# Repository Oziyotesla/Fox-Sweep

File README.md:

# Fox Sweep Half Swept

This is a Ferris Sweep half-swept variant with WeAct BlackPill V2.0 and QMK configuration files.

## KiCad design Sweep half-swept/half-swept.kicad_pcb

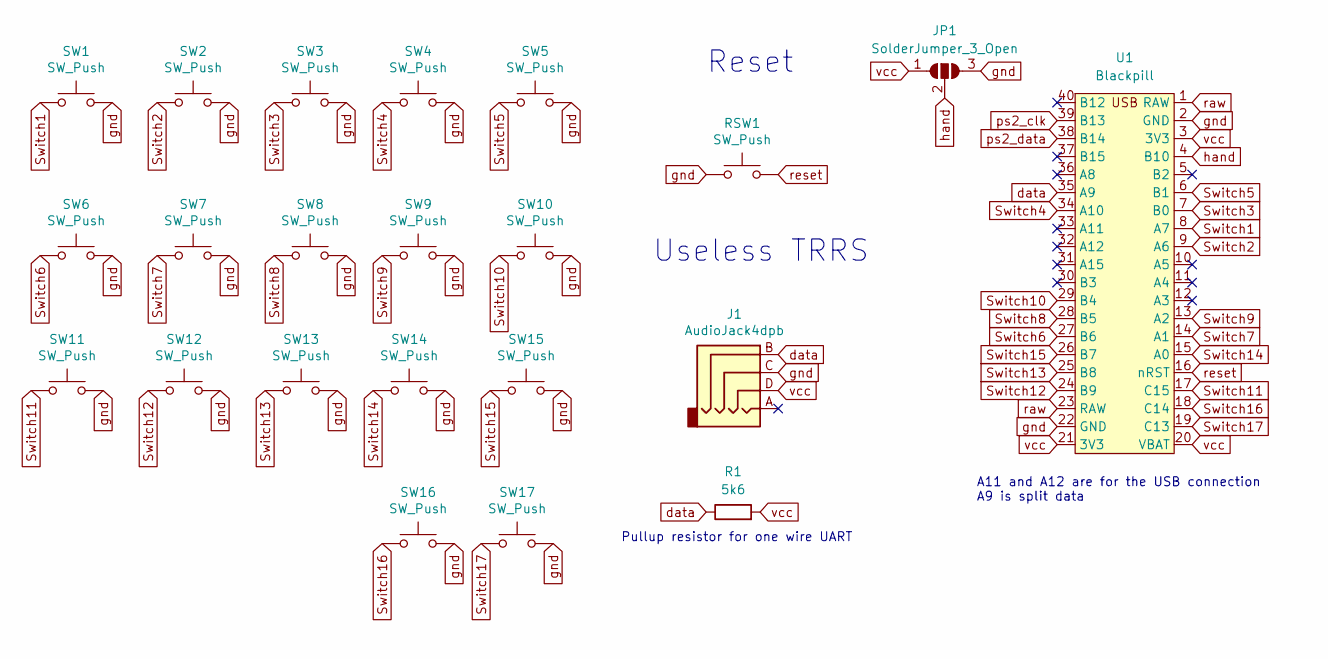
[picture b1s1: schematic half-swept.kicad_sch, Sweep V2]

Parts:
J1: AudioJack4dpb; TRRS 2side
JP1: SolderJumper_3_Open; SolderJumper-3_P1.3mm_Open_RoundedPad1.0x1.5mm
R1: 5k6; 0603 resistor
RSW1: SW_Push; ResetSW
SW1, SW2, SW3, SW4, SW5, SW6, SW7, SW8, SW9, SW10, SW11, SW12, SW13, SW14, SW15, SW16, SW17: SW_Push; SW_PG1350_rev_DPB
U1: Blackpill; Blakpill

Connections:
Switch1: SW1.1, U1.8 (A7)
Switch2: SW2.1, U1.9 (A6)
Switch3: SW3.1, U1.7 (B0)
Switch4: SW4.1, U1.34 (A10)
Switch5: SW5.1, U1.6 (B1)
Switch6: SW6.1, U1.27 (B6)
Switch7: SW7.1, U1.14 (A1)
Switch8: SW8.1, U1.28 (B5)
Switch9: SW9.1, U1.13 (A2)
Switch10: SW10.1, U1.29 (B4)
Switch11: SW11.1, U1.17 (C15)
Switch12: SW12.1, U1.24 (B9)
Switch13: SW13.1, U1.25 (B8)
Switch14: SW14.1, U1.15 (A0)
Switch15: SW15.1, U1.26 (B7)
Switch16: SW16.1, U1.18 (C14)
Switch17: SW17.1, U1.19 (C13)
data: J1.B, R1.1, U1.35 (A9)
hand: JP1.2 (C), U1.4 (B10)
ps2_clk: U1.39 (B13)
ps2_data: U1.38 (B14)
raw: U1.1 (RAW), U1.23 (RAW)
vcc: J1.D, JP1.1 (A), R1.2, U1.3 (3V3), U1.20 (VBAT), U1.21 (3V3)

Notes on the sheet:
A11 and A12 are for the USB connection A9 is split data
Reset
Useless TRRS
Pullup resistor for one wire UART

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
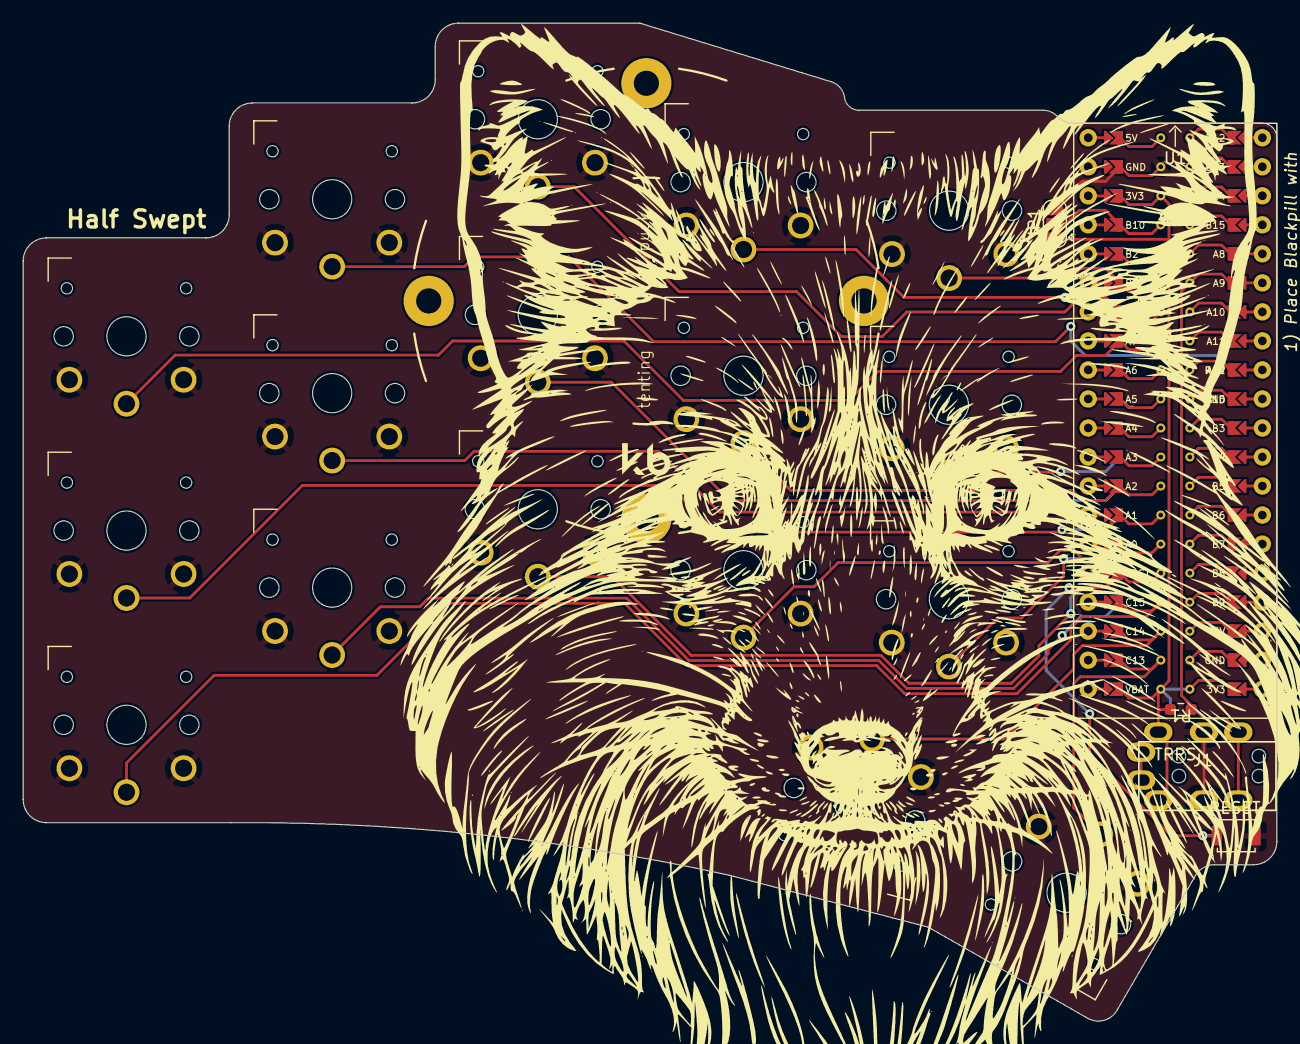
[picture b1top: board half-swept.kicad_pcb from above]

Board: 2 copper layers, 109.7 x 87.3 mm, 22 parts (0 on the bottom side), 23 nets.

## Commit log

2024-01-02 Initial commit
    upload KiCad files and QMK configuration
2024-01-07 Update keymap
2024-01-07 PCB update
    missing pull-up resistor added to one wire serial
2024-01-12 Update gaming layer
    Updated gaming layer StarCraft II
2024-01-13 Update keymap.json
    Updated for fps games and StarCraft 2
2024-03-05 Added another gaming layout
2025-04-10 Altium configuration
    Initial working configuration for altium
2025-04-10 Fix for one scroll at a time fixes altium keymap.
